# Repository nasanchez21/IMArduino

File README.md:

# IMArduino
Repository for the development of an NYUSH IMA Barebones Arduino Uno clone kit.

The goal of this project is to develop a DIY Arduino clone kit that would allow users to manually build their own Arduino Uno clones. The value of this kit is that it has pedagogical value and can also serve as a functional replacement for standard Arduino Uno for many uses.

# Documentation

https://docs.google.com/spreadsheets/d/1-6iVScVSJgVeOGY05u6eFCvq3GYR2P5O7BafCsH0iSc/edit#gid=1137227327

# References

https://store.arduino.cc/usa/arduino-uno-rev3 (within their Documentation tab, have a set of Eagle files that we used as a reference design)

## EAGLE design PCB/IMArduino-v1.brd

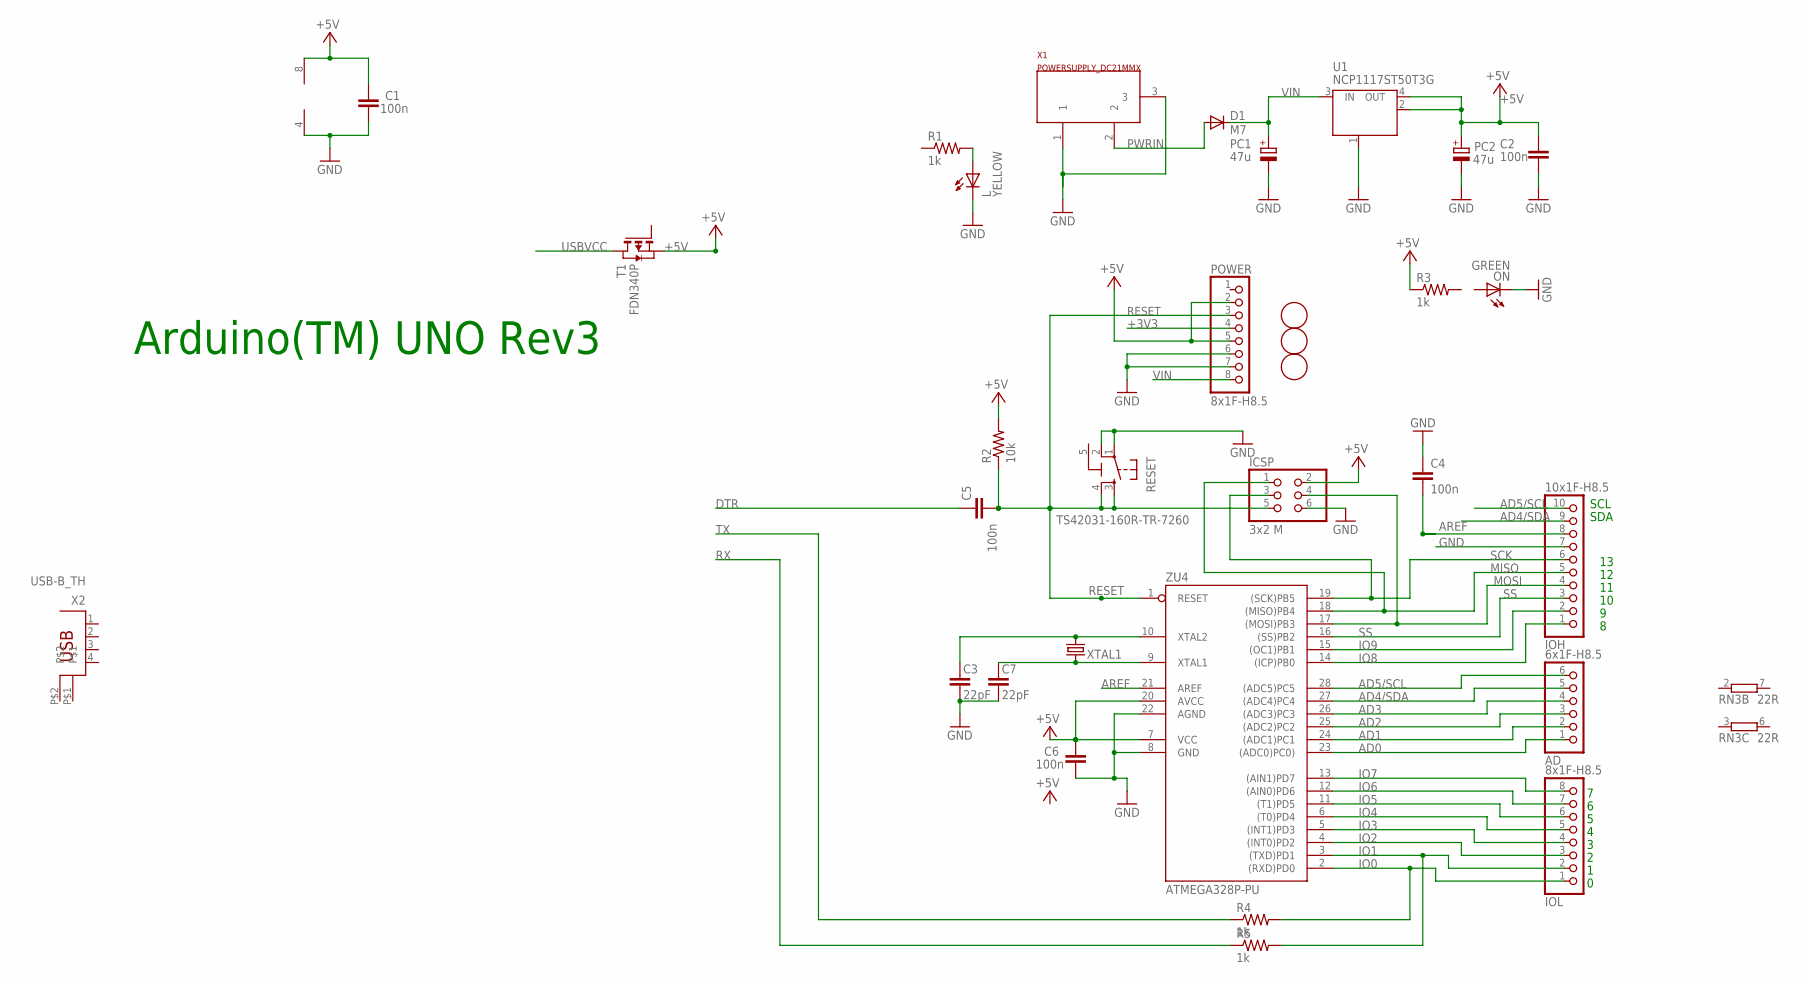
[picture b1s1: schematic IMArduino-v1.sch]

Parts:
AD: 6x1F-H8.5; 1X06
C1, C2, C4, C5, C6: 100n; C0603-ROUND
C3, C7: 22pF; C0603-ROUND
D1: M7; SMB
FD1, FD2, FD3: FIDUCIALMOUNT; FIDUCIA-MOUNT
ICSP: 3x2 M; 2X03
IOH: 10x1F-H8.5; 1X10
IOL: 8x1F-H8.5; 1X08
L: YELLOW; CHIP-LED0805
ON: GREEN; CHIP-LED0805
PC1, PC2: 47u; PANASONIC_D
POWER: 8x1F-H8.5; 1X08
R1, R3, R4, R5: 1k; 0204/7
R2: 10k; 0204/7
RESET: TS42031-160R-TR-7260; TS42
RN3: 22R; CAY16
T1: FDN340P; SOT-23
U1: NCP1117ST50T3G; SOT223
U5: LMV358IDGKR; MSOP08
X1: POWERSUPPLY_DC21MMX; POWERSUPPLY_DC-21MM
X2: USB-B_TH; PN61729
XTAL1: CRYSTALHC49U-V; HC49U-V
ZU4: ATMEGA328P-PU; DIL28-3

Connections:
5-GND: RESET.5 (5-GND)
+3V3: POWER.4
+5V: C1.2, C2.2, C6.2, ICSP.2, PC2.+, POWER.2, POWER.5, R2.2, R3.1, T1.2 (S), U1.2 (OUT), U1.4 (OUT), U5.8 (V+), ZU4.7 (VCC), ZU4.20 (AVCC)
AD0: AD.1, ZU4.23 ((ADC0)PC0))
AD1: AD.2, ZU4.24 ((ADC1)PC1)
AD2: AD.3, ZU4.25 ((ADC2)PC2)
AD3: AD.4, ZU4.26 ((ADC3)PC3)
AD4/SDA: AD.5, IOH.9, ZU4.27 ((ADC4)PC4)
AD5/SCL: AD.6, IOH.10, ZU4.28 ((ADC5)PC5)
AREF: C4.2, IOH.8, ZU4.21 (AREF)
DTR: C5.1
GND: C1.1, C2.1, C3.1, C4.1, C6.1, C7.1, ICSP.6, IOH.7, L.C, ON.C, PC1.-, PC2.-, POWER.6, POWER.7, RESET.1, RESET.2, U1.1 (GND/ADJ), U5.4 (V-), X1.1, X1.3, ZU4.8 (GND), ZU4.22 (AGND)
IO0: IOL.1, R4.2, ZU4.2 ((RXD)PD0)
IO1: IOL.2, R5.2, ZU4.3 ((TXD)PD1)
IO2: IOL.3, ZU4.4 ((INT0)PD2)
IO3: IOL.4, ZU4.5 ((INT1)PD3)
IO4: IOL.5, ZU4.6 ((T0)PD4)
IO5: IOL.6, ZU4.11 ((T1)PD5)
IO6: IOL.7, ZU4.12 ((AIN0)PD6)
IO7: IOL.8, ZU4.13 ((AIN1)PD7)
IO8: IOH.1, ZU4.14 ((ICP)PB0)
IO9: IOH.2, ZU4.15 ((OC1)PB1)
MISO: ICSP.1, IOH.5, ZU4.18 ((MISO)PB4)
MOSI: ICSP.4, IOH.4, ZU4.17 ((MOSI)PB3)
unnamed: L.A, R1.2
PWRIN: D1.A, X1.2
RESET: C5.2, ICSP.5, POWER.3, R2.1, RESET.3, RESET.4, ZU4.1 (RESET)
RX: R5.1
SCK: ICSP.3, IOH.6, ZU4.19 ((SCK)PB5)
SS: IOH.3, ZU4.16 ((SS)PB2)
TX: R4.1
USBVCC: T1.1 (D)
VIN: D1.C, PC1.+, POWER.8, U1.3 (IN)
XTAL1: C7.2, XTAL1.1, ZU4.9 (XTAL1)
XTAL2: C3.2, XTAL1.2, ZU4.10 (XTAL2)

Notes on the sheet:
Arduino(TM) UNO Rev3
SDA
SCL

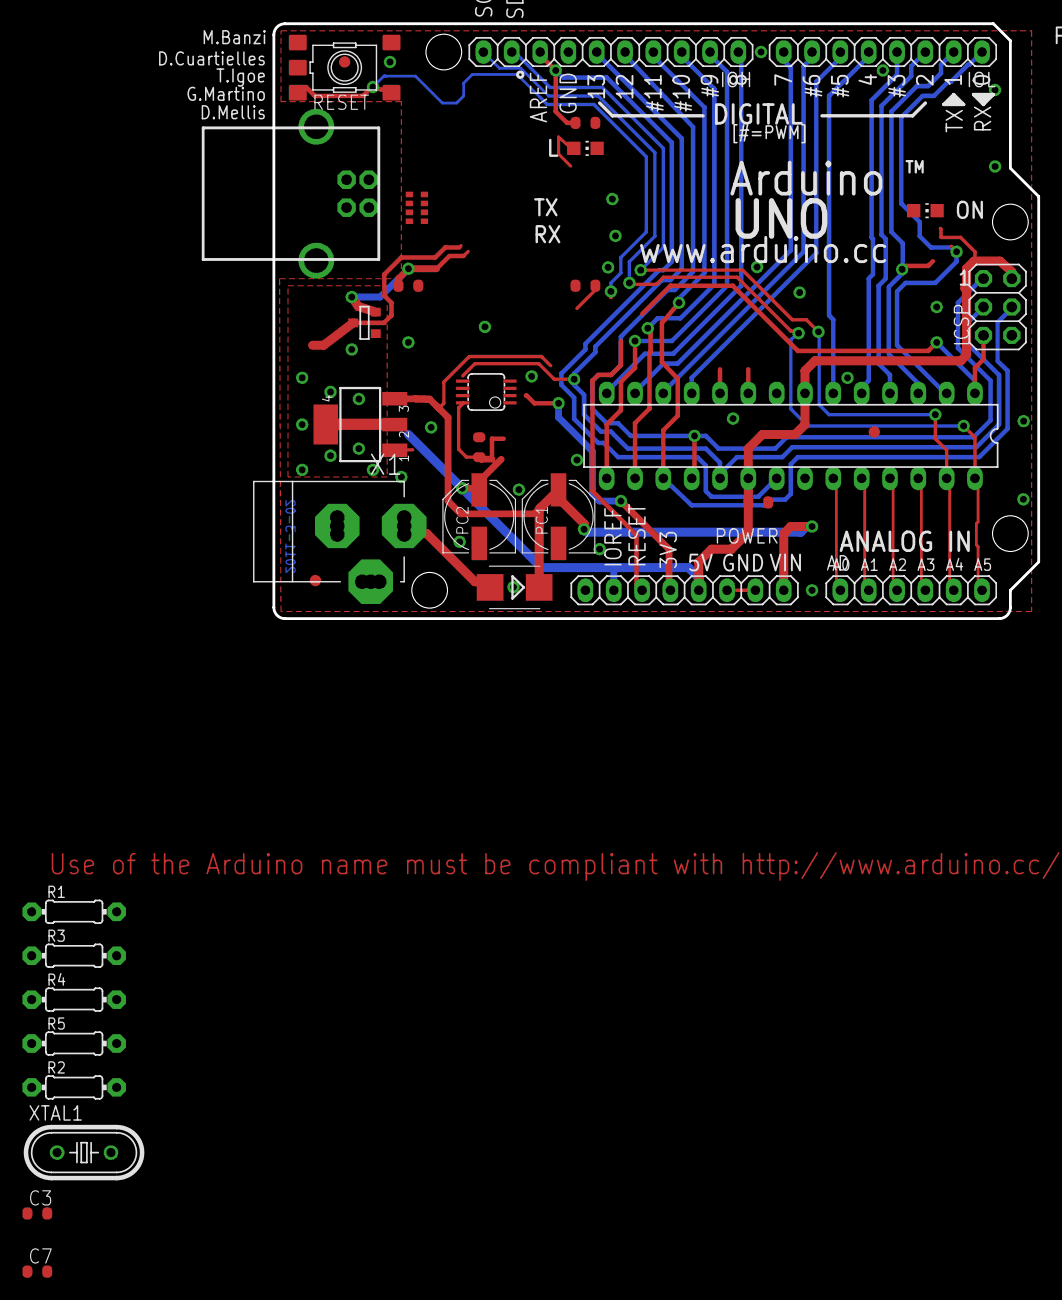
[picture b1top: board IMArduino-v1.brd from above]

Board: 2 copper layers, 68.6 x 53.3 mm, 34 parts (0 on the bottom side), 29 nets.

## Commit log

2019-05-11 first design
2019-05-13 7805 footprint changed to TO-220, Readme updated
2019-05-14 corrections after testing
